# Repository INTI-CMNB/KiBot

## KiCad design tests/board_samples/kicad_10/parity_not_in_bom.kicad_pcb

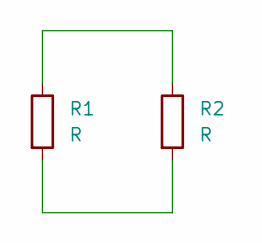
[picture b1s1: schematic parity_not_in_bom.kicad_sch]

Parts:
R1, R2: R; R_0805_2012Metric

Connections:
unnamed: R1.1, R2.1
unnamed: R1.2, R2.2

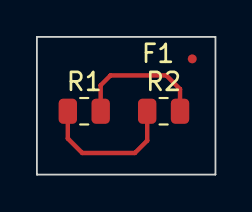
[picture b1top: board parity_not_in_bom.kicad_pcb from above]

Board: 2 copper layers, 9.9 x 7.7 mm, 3 parts (0 on the bottom side), 2 nets.

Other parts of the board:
F1: Fiducial_0.5mm_Mask1.5mm

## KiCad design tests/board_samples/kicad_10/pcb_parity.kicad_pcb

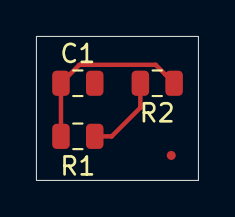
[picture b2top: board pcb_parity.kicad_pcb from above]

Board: 2 copper layers, 9.0 x 8.0 mm, 4 parts (0 on the bottom side), 2 nets.

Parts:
C1: 1uF; C_0805_2012Metric
F1: Fiducial_0.5mm_Mask1.5mm
R1: 100; R_0805_2012Metric
R2: 200; R_0805_2012Metric

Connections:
unnamed: C1.1, R1.2, R2.1
VCC: R1.1, R2.2

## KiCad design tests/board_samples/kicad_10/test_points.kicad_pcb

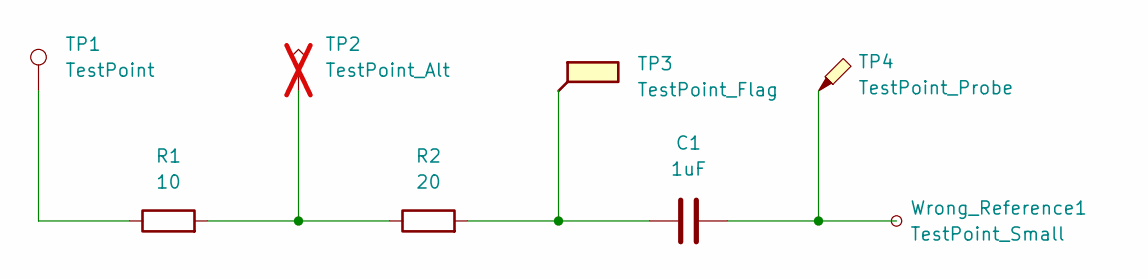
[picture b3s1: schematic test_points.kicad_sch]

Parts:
C1: 1uF; C_0805_2012Metric
R1: 10; R_0805_2012Metric
R2: 20; R_0805_2012Metric
TP1: TestPoint; TestPoint_Loop_D1.80mm_Drill1.0mm_Beaded
TP2: TestPoint_Alt; TestPoint_Pad_1.0x1.0mm; not fitted
TP3: TestPoint_Flag; TestPoint_Plated_Hole_D2.0mm
TP4: TestPoint_Probe; TestPoint_Pad_D2.0mm
Wrong_Reference1: TestPoint_Small; TestPoint_Pad_D1.0mm

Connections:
unnamed: C1.1, R2.2, TP3.1
unnamed: C1.2, TP4.1, Wrong_Reference1.1
unnamed: R1.1, TP1.1
unnamed: R1.2, R2.1, TP2.1

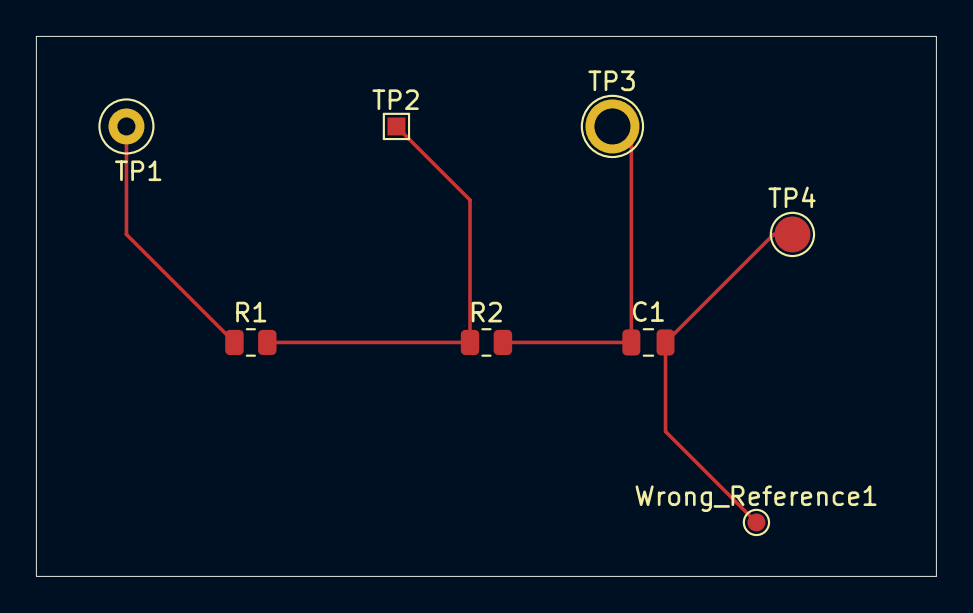
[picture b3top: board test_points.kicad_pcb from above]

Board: 2 copper layers, 50.0 x 30.0 mm, 8 parts (0 on the bottom side), 4 nets.
